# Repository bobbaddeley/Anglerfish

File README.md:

# Anglerfish
Anglerfish for Bikes is a project to help people locate their bicycles at night. It uses Bluetooth Low Energy, so you can use either the remote or your smartphone. Simply press the button and the globe on your bike will light up with your customized pattern, letting you know where your bike is.

## Current Status - 2015/08/17

This project is currently at Working Prototype status. The firmware works, the electronics work, the mechanicals work, and in practice it works. There are still a lot of things necessary to turn this from a project to a product. A lot of refinement and cleaning to make the parts easier to assemble, more robust (especially the transmitter), and making it easier to install.

Here's a video of the status, plus it working in a practical situation. Woo! There won't be any additional development until after Burning Man, when I can learn from it in a real environment and figure out what needs to be refined.

## Licenses

Because we use a module, we should be ok with the FCC. The other circuitry may still need to be tested for unintentional transmission, but it's extremely unlikely that it would cause any problems.

Use of the Bluetooth logo is limited, and I think even using the word may be a problem with the Bluetooth SIG. If this project ever seeks commercialization, we'll have to deal with that.

I haven't looked into the use of the Anglerfish name for trademarks, and I haven't looked to see if this idea violates any patents.

I am not using any proprietary or restricted code.

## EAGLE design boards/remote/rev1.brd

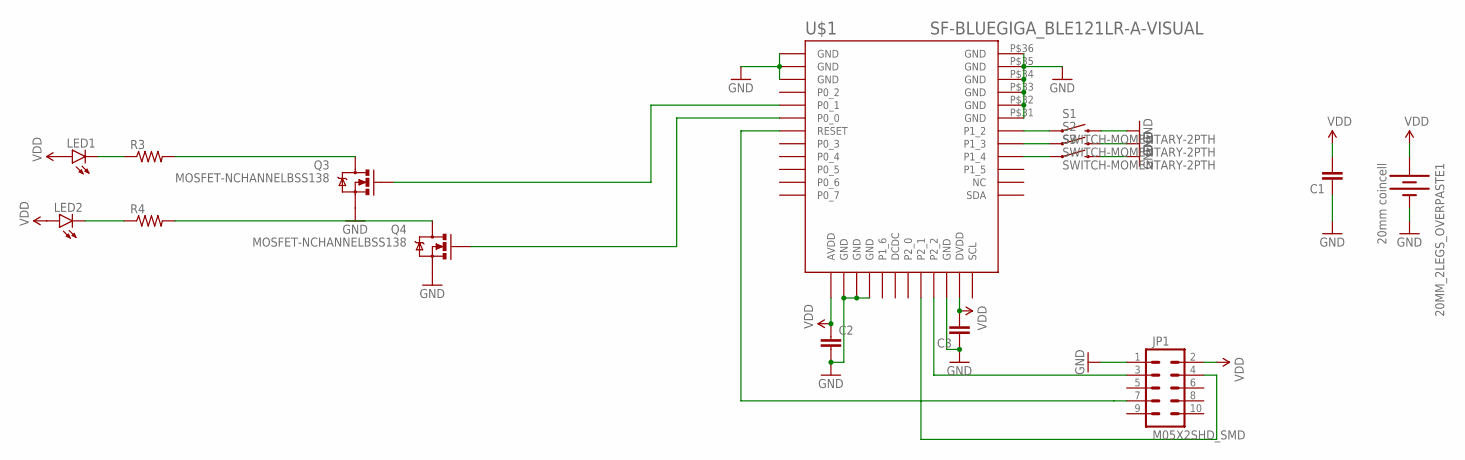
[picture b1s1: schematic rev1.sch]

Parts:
20MM_2LEGS_OVERPASTE1: 20mm coincell; BATTCON_20MM_4LEGS
C1: CAP1206; 1206
C2, C3: CAP0603-CAP; 0603-CAP
JP1: M05X2SHD_SMD; 2X5-SHROUDED_SMD
LED1, LED2: LED1206; LED-1206
Q3, Q4: MOSFET-NCHANNELBSS138; SOT23-3
R3, R4: RESISTOR0603; 0603-RES
S1, S2, S3: SWITCH-MOMENTARY-2PTH; TACTILE-PTH
U$1: SF-BLUEGIGA_BLE121LR-A-VISUAL; SF-BLUEGIGA_BLE121LR-A

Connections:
GND: 20MM_2LEGS_OVERPASTE1.2 (-), C1.1, C2.2, C3.1, JP1.1, Q3.2 (S), Q4.2 (S), S1.3 (2), S2.3 (2), S3.3 (2), U$1.P$1 (GND), U$1.P$2 (GND), U$1.P$3 (GND), U$1.P$14 (GND), U$1.P$15 (GND), U$1.P$16 (GND), U$1.P$22 (GND), U$1.P$31 (GND), U$1.P$32 (GND), U$1.P$33 (GND), U$1.P$34 (GND), U$1.P$35 (GND), U$1.P$36 (GND)
unnamed: Q4.1 (G), U$1.P$6 (P0_0)
unnamed: S1.1, U$1.P$30 (P1_2)
unnamed: S2.1, U$1.P$29 (P1_3)
unnamed: S3.1, U$1.P$28 (P1_4)
unnamed: Q3.3 (D), R3.2
unnamed: Q4.3 (D), R4.2
unnamed: Q3.1 (G), U$1.P$5 (P0_1)
unnamed: LED1.C, R3.1
unnamed: JP1.3, U$1.P$21 (P2_2)
unnamed: JP1.4, U$1.P$20 (P2_1)
unnamed: JP1.7, U$1.P$7 (RESET)
unnamed: LED2.C, R4.1
VDD: 20MM_2LEGS_OVERPASTE1.1 (+), C1.2, C2.1, C3.2, JP1.2, LED1.A, LED2.A, U$1.P$13 (AVDD), U$1.P$23 (DVDD)

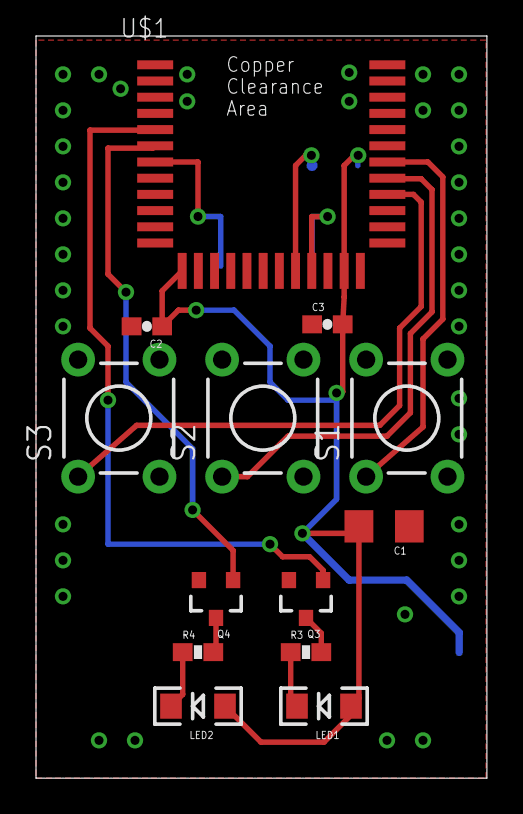
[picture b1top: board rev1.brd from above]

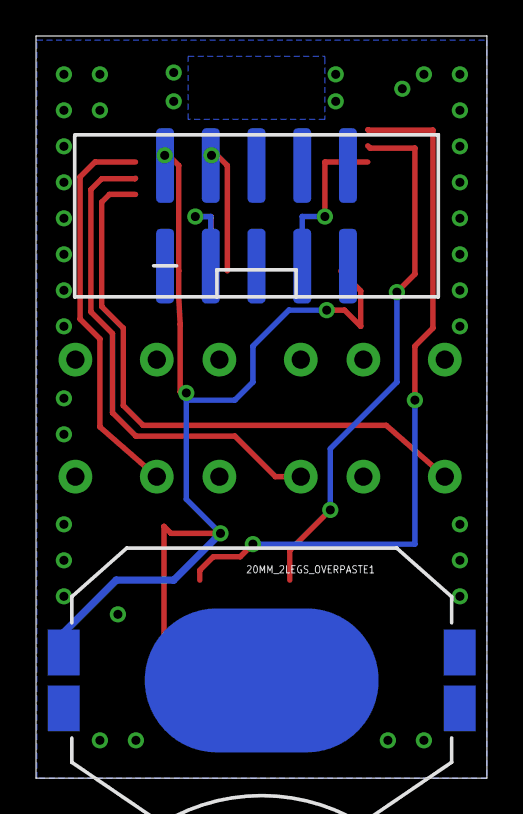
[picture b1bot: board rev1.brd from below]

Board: 2 copper layers, 25.1 x 41.2 mm, 15 parts (2 on the bottom side), 14 nets.

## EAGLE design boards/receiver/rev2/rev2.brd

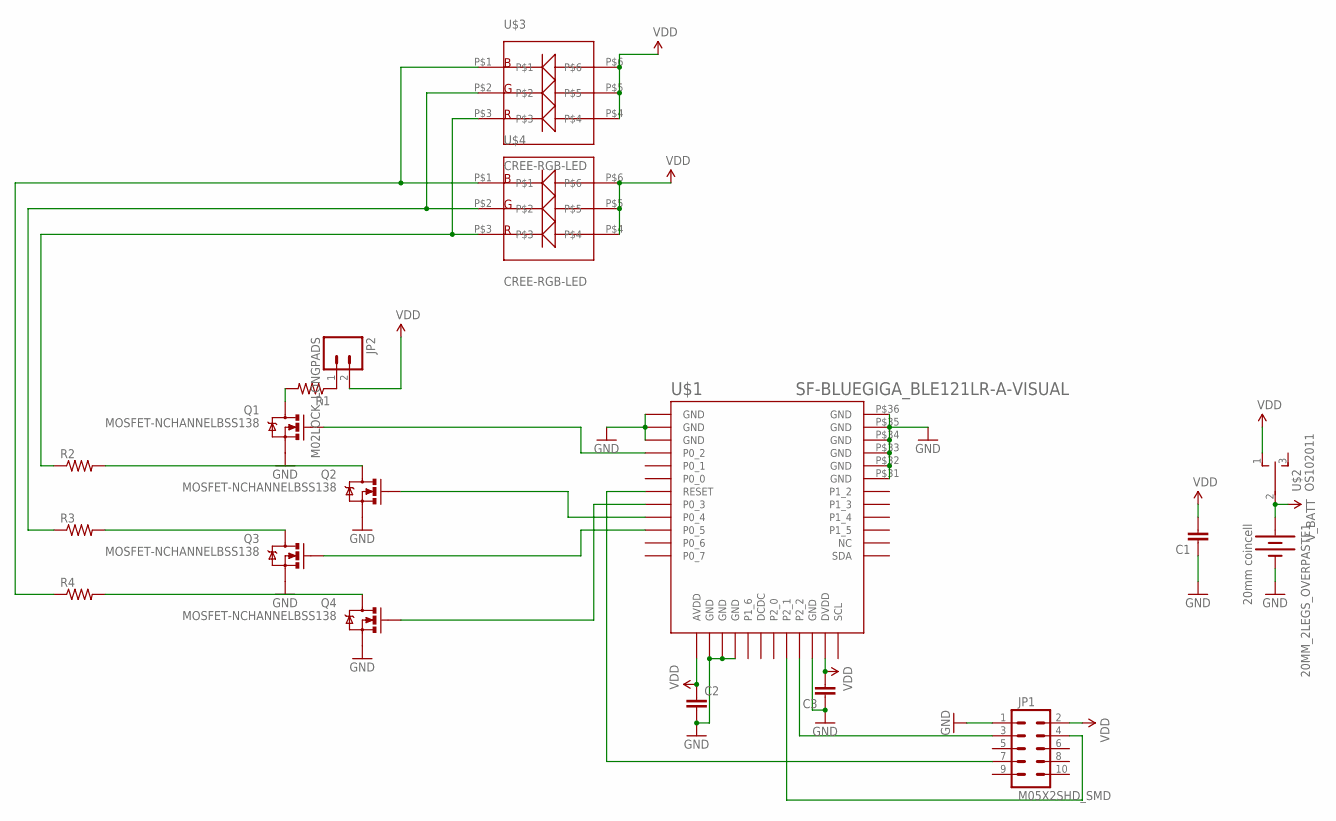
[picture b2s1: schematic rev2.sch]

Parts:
20MM_2LEGS_OVERPASTE1: 20mm coincell; BATTCON_20MM_4LEGS
C1: CAP1206; 1206
C2, C3: CAP0603-CAP; 0603-CAP
JP1: M05X2SHD_SMD; 2X5-SHROUDED_SMD
JP2: M02LOCK_LONGPADS; 1X02_LOCK_LONGPADS
Q1, Q2, Q3, Q4: MOSFET-NCHANNELBSS138; SOT23-3
R1, R2, R3, R4: RESISTOR0603; 0603-RES
U$1: SF-BLUEGIGA_BLE121LR-A-VISUAL; SF-BLUEGIGA_BLE121LR-A
U$2: OS102011
U$3, U$4: CREE-RGB-LED

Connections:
GND: 20MM_2LEGS_OVERPASTE1.2 (-), C1.1, C2.2, C3.1, JP1.1, Q1.2 (S), Q2.2 (S), Q3.2 (S), Q4.2 (S), U$1.P$1 (GND), U$1.P$2 (GND), U$1.P$3 (GND), U$1.P$14 (GND), U$1.P$15 (GND), U$1.P$16 (GND), U$1.P$22 (GND), U$1.P$31 (GND), U$1.P$32 (GND), U$1.P$33 (GND), U$1.P$34 (GND), U$1.P$35 (GND), U$1.P$36 (GND)
unnamed: Q1.3 (D), R1.2
unnamed: Q2.3 (D), R2.2
unnamed: Q3.3 (D), R3.2
unnamed: Q4.3 (D), R4.2
unnamed: Q4.1 (G), U$1.P$8 (P0_3)
unnamed: Q3.1 (G), U$1.P$10 (P0_5)
unnamed: Q2.1 (G), U$1.P$9 (P0_4)
unnamed: Q1.1 (G), U$1.P$4 (P0_2)
unnamed: JP2.1, R1.1
unnamed: R2.1, U$3.P$3, U$4.P$3
unnamed: R3.1, U$3.P$2, U$4.P$2
unnamed: JP1.3, U$1.P$21 (P2_2)
unnamed: JP1.4, U$1.P$20 (P2_1)
unnamed: JP1.7, U$1.P$7 (RESET)
unnamed: R4.1, U$3.P$1, U$4.P$1
VDD: C1.2, C2.1, C3.2, JP1.2, JP2.2, U$1.P$13 (AVDD), U$1.P$23 (DVDD), U$2.1 (O), U$3.P$4, U$3.P$5, U$3.P$6, U$4.P$4, U$4.P$5, U$4.P$6
V_BATT: 20MM_2LEGS_OVERPASTE1.1 (+), U$2.2

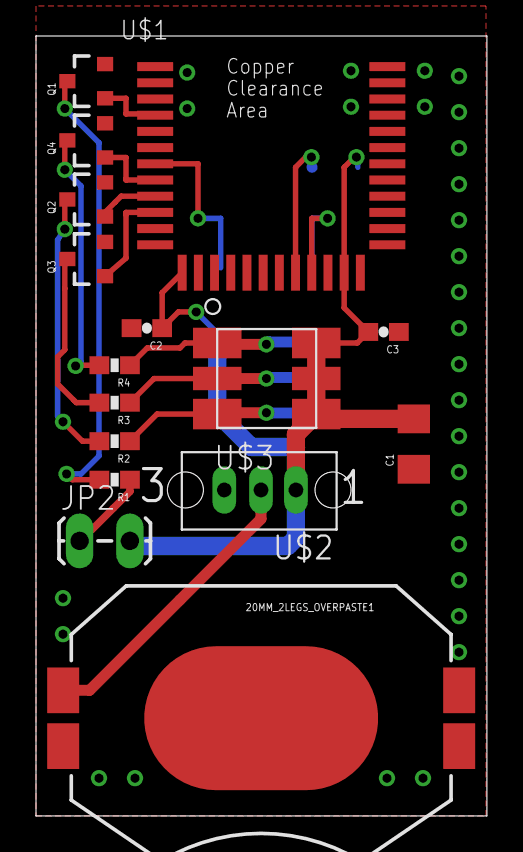
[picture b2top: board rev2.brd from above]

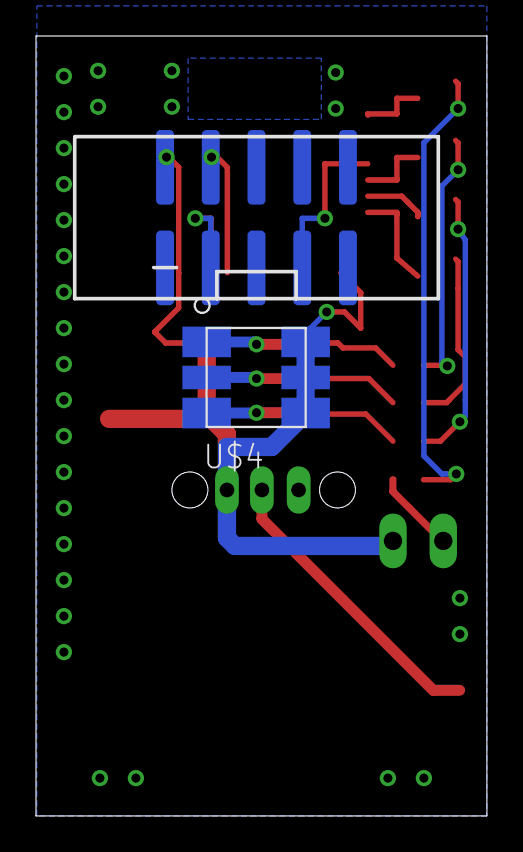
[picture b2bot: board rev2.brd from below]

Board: 2 copper layers, 25.1 x 43.3 mm, 18 parts (2 on the bottom side), 18 nets.

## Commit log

2015-08-17 Initial commit of everything
2015-08-17 Adding to the readme

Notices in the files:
parts and their libraries:
SparkFun-DiscreteSemi: Licensing: Creative Commons ShareAlike 4.0 International - https://creativecommons.org/licenses/by-sa/4.0
